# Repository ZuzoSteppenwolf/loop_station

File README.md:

# loop_station
Cross Innovation Class Team Bukea

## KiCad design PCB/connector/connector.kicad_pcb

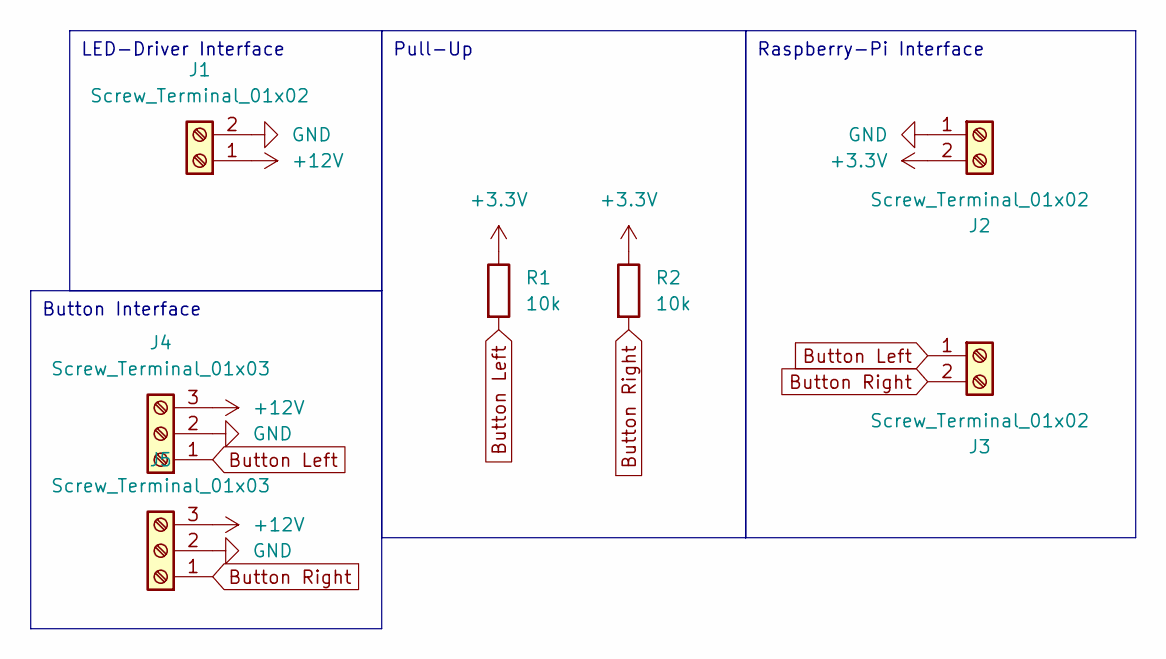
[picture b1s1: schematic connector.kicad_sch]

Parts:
J1, J2, J3: Screw_Terminal_01x02; TerminalBlock_TE_282834-2_1x02_P2.54mm_Horizontal
J4, J5: Screw_Terminal_01x03; TerminalBlock_TE_282834-3_1x03_P2.54mm_Horizontal
R1, R2: 10k; R_Axial_DIN0204_L3.6mm_D1.6mm_P2.54mm_Vertical

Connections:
+3.3V: J2.2, R1.1, R2.1
+12V: J1.1, J4.3, J5.3
Button Left: J3.1, J4.1, R1.2
Button Right: J3.2, J5.1, R2.2
GND: J1.2, J2.1, J4.2, J5.2

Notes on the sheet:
Pull-Up
Button Interface
Raspberry-Pi Interface
LED-Driver Interface

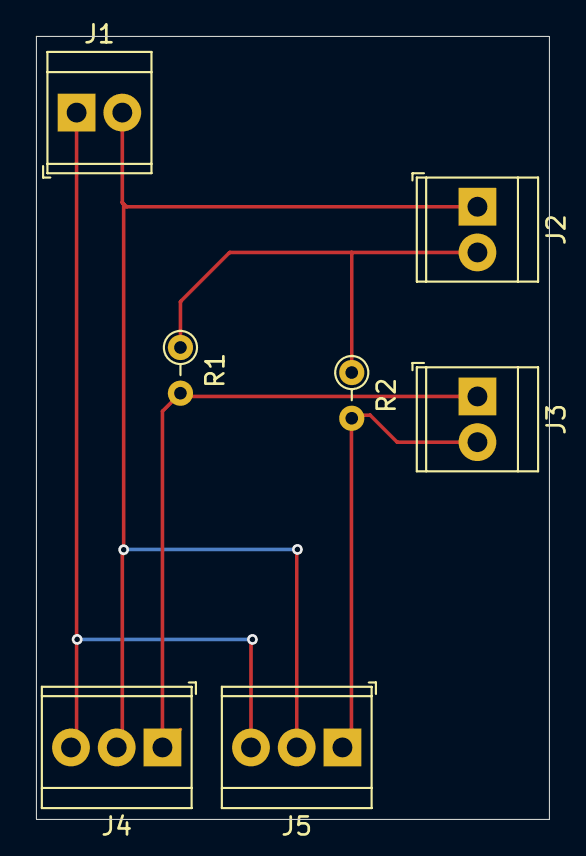
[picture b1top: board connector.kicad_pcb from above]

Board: 2 copper layers, 28.5 x 43.5 mm, 7 parts (0 on the bottom side), 5 nets.

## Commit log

2024-06-13 create mvn project: auto structure
2024-06-13 ignore dirs: .idea; .vscode; target
2024-06-25 gui java21
2024-06-25 converted to "pi" Project; cleaned
2024-06-25 qr code
2024-06-25 qr code undone
2024-06-25 gpio
2024-06-25 Action on KEY_RELEASED
2024-06-29 Fullscreen
2024-06-30 ignore
2024-07-01 disabled the infotext
2024-07-01 curser invisible; rewardscreen stage fix bug: mutiple windows -> first current stage close
2024-07-04 Topic Pools with questions
2024-07-04 Static Topic-Pools
2024-07-06 implemented lost game scenario, modified the Question class so that a fun fact/explanation belongs to a certain question
2024-07-08 funfact screen with stackpane
2024-07-08 correct java version for xml
2024-07-08 added final Question to pools; Pools used in uicontroller; funfacttext and questiontext -> auto new line
2024-07-08 xml version
2024-07-08 playing with colors
2024-07-08 execution jar; spot for raspberry pi update
2024-07-08 make it runable on raspberrypi
2024-07-08 alignment
2024-07-10 Name change; validation fedback; bottom change
2024-07-10 funfact text alignment
2024-07-10 inline Docu
2024-07-10 functional QR-Code
2024-07-10 funfact scene bottom center
2024-08-01 AMD Doc
2024-08-07 connector plate
